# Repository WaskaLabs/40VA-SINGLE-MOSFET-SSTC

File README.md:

# 40VA-SINGLE-MOSFET-SSTC

If anyone would like to cooperate on the project or interrupt designs, have any questions or comments, feel free to contact me.

For more pictures and videos of the coil in action go to : https://www.instagram.com/waskalabs/

After posting some pictures of my completed design I have had quite a few people ask me for schematics / files / build info. The original intention of the design was to create a single pcb driver for any possible configuration of moderately low voltage transformer based tesla coils that I could use as a simple and quick platform for developing a variety of small desktop tesla coil designs and learn more about sstc operation. This design is a mixture of steve wards class e and mini sstc builds with some small modifications. For detials on the design go to (https://www.stevehv.4hv.org/sstc5.htm). I developed the V0 pcb design to be milled out at home using a pcb mill using a ~0.5mm endmill. You dont have to use a mill here - thats just what I designed the tolerances for. Any method of diy pcb production should work. After developing and testing the driver I put together a small test coil, tuned everything, and had a relatively impressive mini coil in about a day. The V0 design has a well annotated schematic and pcb with descriptions and information that will hopefully be easy for the novice to understand and recreate. There are many online resources for understanding the general operation of SSTCs so I will not be covering everything in detail here but only explaining the specs of my mini coil build here (links to more general resources below).

The V1 pcb design has been designed for proper pcb production and includes good high power design, external interrputer pins, better wire connection points, and has been made to be configurable for use with raw mains power using an external transformer as the low voltage source. As of writing this the pcbs are currently in production and have not arrived yet. When they do I will be testing mains versions of the design as well as some modular addons I have come up with and will post the designs here.

# mini coil design specifications  (V0 pcb):

Secondary coil = ~ 5.5 inch 34awg secondary coil wound on 3.5 inch pvc ~ 430khz (also tested with a ~6.5" 395khz coil which gave even better results)

Primary coil   = ~ 4.5 inch, 3 turns, 14 awg braided wire

Transformer    = UL1585 24v 40va (white and black wires for 120v)

555 interrupt  = ~ 7 - 480hz

Bus capacitors = 2 x 35v 22000uf caps

Mosfet         = IRFP460 (use for any high frequency coil)

After powering up the first coil and playing around with it a bit - it became immediately apparent that the 555 interrupter is not the way to go. I left it on the design as a simple way to get started - but I would not recommend it for continual use. The issue is the "On time" (time that the coil is powered up on each pulse) is much longer than necessary. The coil would ramp up and generate an arc, but would continue to burn away in continuous wave operation until being switched off by the low pulse of the 555. This can cause unnecessary strain on the mosfet, drains the bus caps, and also takes away from the aesthetic of the larger arcs. My solution to this was to remove the 555 chip and solder a 3 pin male to female dupont wire to the chip socket (interrupt, 12v, gnd pins) and run it into an arduino nano clone (pin 9, vin, gnd, respectively). The arduino should be programmed to give an on-time of between 1 - 5 milliseconds (I have stuck with 2 ms). I haave decided to add a potentiometer to vary the off time of the design to cycle between 2 - 1000 hz. The arduino tone library was also used successfully create audio output.

I will not be adding any more detail about the interrupter designs until the V1 pcbs are complete. Once they are in and test coils are built I will be making various interrupter addons such as staccato mode, isolated audio input, multiple potentiometers for varied on and off times over a given range, etc. And will post finished developments here.

If you decided to use an atx power supply as a case like I did. Be sure to keep the primary coil atleast 1-2 inches away from the metal surface of the case as the steel will interfere with the coil and significantly reduce performance. I 3D printed a coil standoff for this

For more detailed explainations of sstc operation & design:

https://www.stevehv.4hv.org/sstcindex.htm

https://www.loneoceans.com/labs/#

http://kaizerpowerelectronics.dk/

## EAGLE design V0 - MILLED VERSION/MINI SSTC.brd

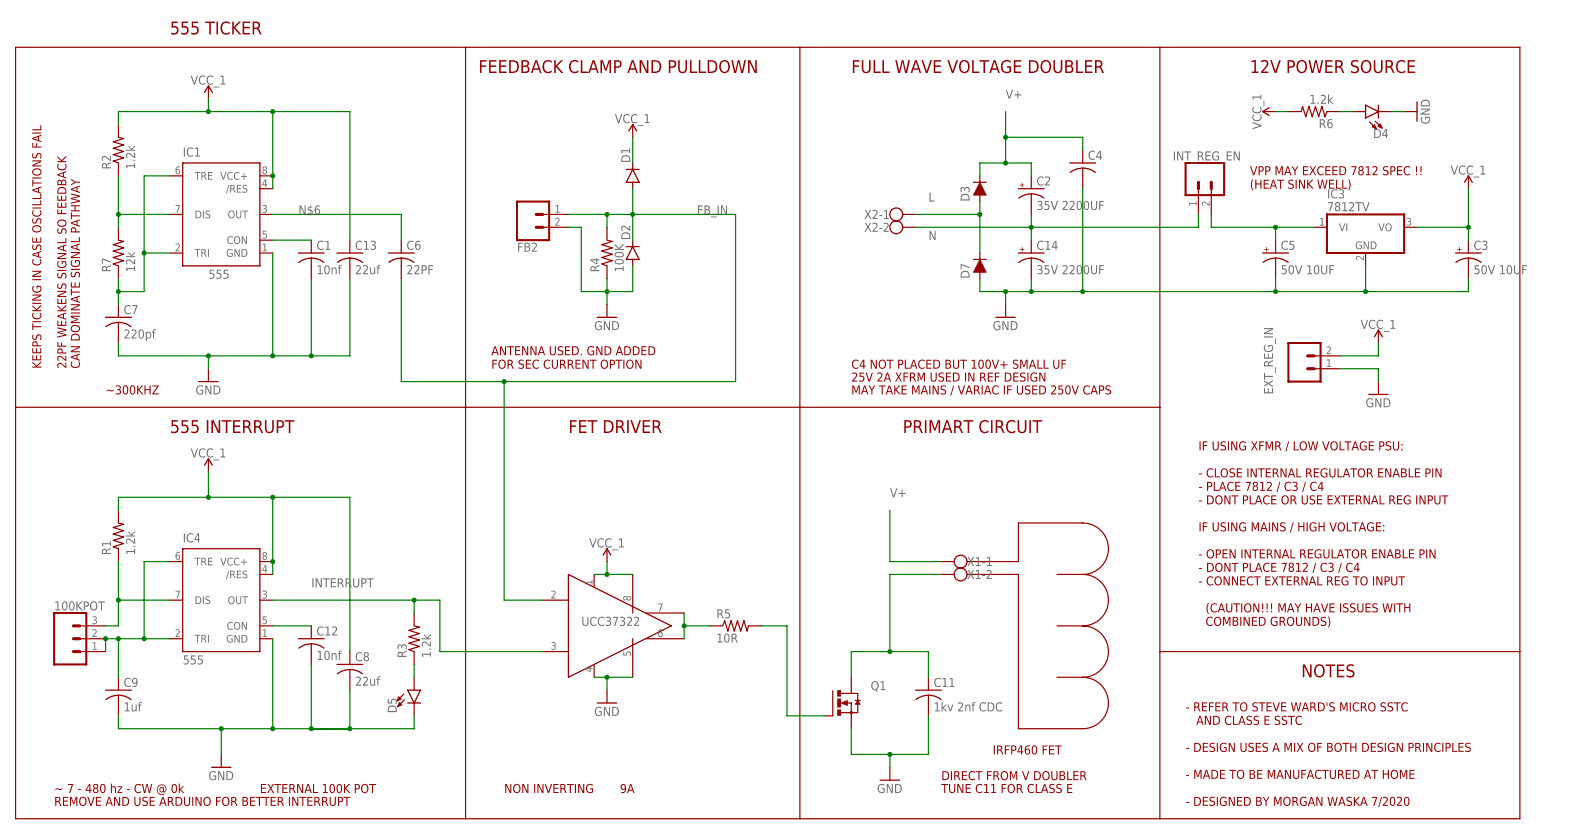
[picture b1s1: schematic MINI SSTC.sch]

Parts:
100KPOT: 455-1750-1-ND; 1X03
C1, C12: 10nf; C025-040X050
C2, C14: 35V 2200UF; E7,5-18
C3, C5: 50V 10UF; E2,5-5
C4: C-US025-040X050; C025-040X050
C6: 22PF; C025-040X050
C7: 220pf; C025-040X050
C8, C13: 22uf; C025-040X050
C9: 1uf; C025-040X050
C11: 1kv 2nf CDC; C150-054X183
D1, D2: 1N4148DO35-7; DO35-7
D3, D7: MUR460; DIODE-1N4001-KIT
D4, D5: LED5MM; LED_5MM
EXT_REG_IN: CONN_02; 1X02
FB2: CONN_02; 1X02
IC1, IC4: 555; DIP08-KIT
IC2: UCC37322; DIL08
IC3: 7812TV; TO220V
INT_REG_EN: CONN_02; 1X02
Q1: IRFP460; TO247BV
R1, R2, R3, R6: 1.2k; 0207/9
R4: 100K; 0207/9
R5: 10R; 0207/9
R7: 12k; 0207/9
X1, X2: W237-102

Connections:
555CONA: C1.1, IC1.5 (CON)
555CONB: C12.1, IC4.5 (CON)
FB_IN: C6.2, D1.A, D2.C, FB2.1, IC2.2 (2_IN), R4.2
GND: C1.2, C3.-, C4.2, C5.-, C7.2, C8.2, C9.2, C11.2, C12.2, C13.2, C14.-, D2.A, D4.K (C), D5.K (C), D7.A, EXT_REG_IN.1, FB2.2, IC1.1 (GND), IC2.4 (4_AGND), IC2.5 (5_PGND), IC3.2 (GND), IC4.1 (GND), Q1.S, R4.1
INTERRUPT: IC2.3 (3_ENBL), IC4.3 (OUT), R3.2
L: D3.A, D7.C, X2.1
N: C2.-, C14.+, INT_REG_EN.1, X2.2
unnamed: Q1.G, R5.2
unnamed: D5.A, R3.1
unnamed: C11.1, Q1.D, X1.2
unnamed: D4.A, R6.1
unnamed: C5.+, IC3.1 (VI), INT_REG_EN.2
unnamed: C6.1, IC1.3 (OUT)
unnamed: IC2.6 (6_OUT), IC2.7 (7_OUT), R5.1
RR555A: IC1.7 (DIS), R2.1, R7.2
RR555B: 100KPOT.3, IC4.7 (DIS), R1.1
TRIG555A: C7.1, IC1.2 (TRI), IC1.6 (TRE), R7.1
TRIG555B: 100KPOT.1, 100KPOT.2, C9.1, IC4.2 (TRI), IC4.6 (TRE)
V+: C2.+, C4.1, D3.C, X1.1
VCC_1: C3.+, C8.1, C13.1, D1.C, EXT_REG_IN.2, IC1.4 (/RES), IC1.8 (VCC+), IC2.1 (1_VDD), IC2.8 (8_VDD), IC3.3 (VO), IC4.4 (/RES), IC4.8 (VCC+), R1.2, R2.2, R6.2

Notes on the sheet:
UCC37322
555 TICKER
555 INTERRUPT
FEEDBACK CLAMP AND PULLDOWN
FET DRIVER
PRIMART CIRCUIT
FULL WAVE VOLTAGE DOUBLER
12V POWER SOURCE
NON INVERTING
~ 7 - 480 hz - CW @ 0k
EXTERNAL 100K POT
~300KHZ
KEEPS TICKING IN CASE OSCILLATIONS FAIL
ANTENNA USED. GND ADDED FOR SEC CURRENT OPTION
25V 2A XFRM USED IN REF DESIGN
MAY TAKE MAINS / VARIAC IF USED 250V CAPS
IF USING XFMR / LOW VOLTAGE PSU: - CLOSE INTERNAL REGULATOR ENABLE PIN - PLACE 7812 / C3 / C4 - DONT PLACE OR USE EXTERNAL REG INPUT IF USING MAINS / HIGH VOLTAGE: - OPEN INTERNAL REGULATOR ENABLE PIN - DONT PLACE 7812 / C3 / C4 - CONNECT EXTERNAL REG TO INPUT (CAUTION!!! MAY HAVE ISSUES WITH COMBI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
DIRECT FROM V DOUBLER
IRFP460 FET
NOTES
- REFER TO STEVE WARD'S MICRO SSTC AND CLASS E SSTC - DESIGN USES A MIX OF BOTH DESIGN PRINCIPLES - MADE TO BE MANUFACTURED AT HOME - DESIGNED BY MORGAN WASKA 7/2020
REMOVE AND USE ARDUINO FOR BETTER INTERRUPT
C4 NOT PLACED BUT 100V+ SMALL UF
VPP MAY EXCEED 7812 SPEC !! (HEAT SINK WELL)
TUNE C11 FOR CLASS E
22PF WEAKENS SIGNAL SO FEEDBACK CAN DOMINATE SIGNAL PATHWAY

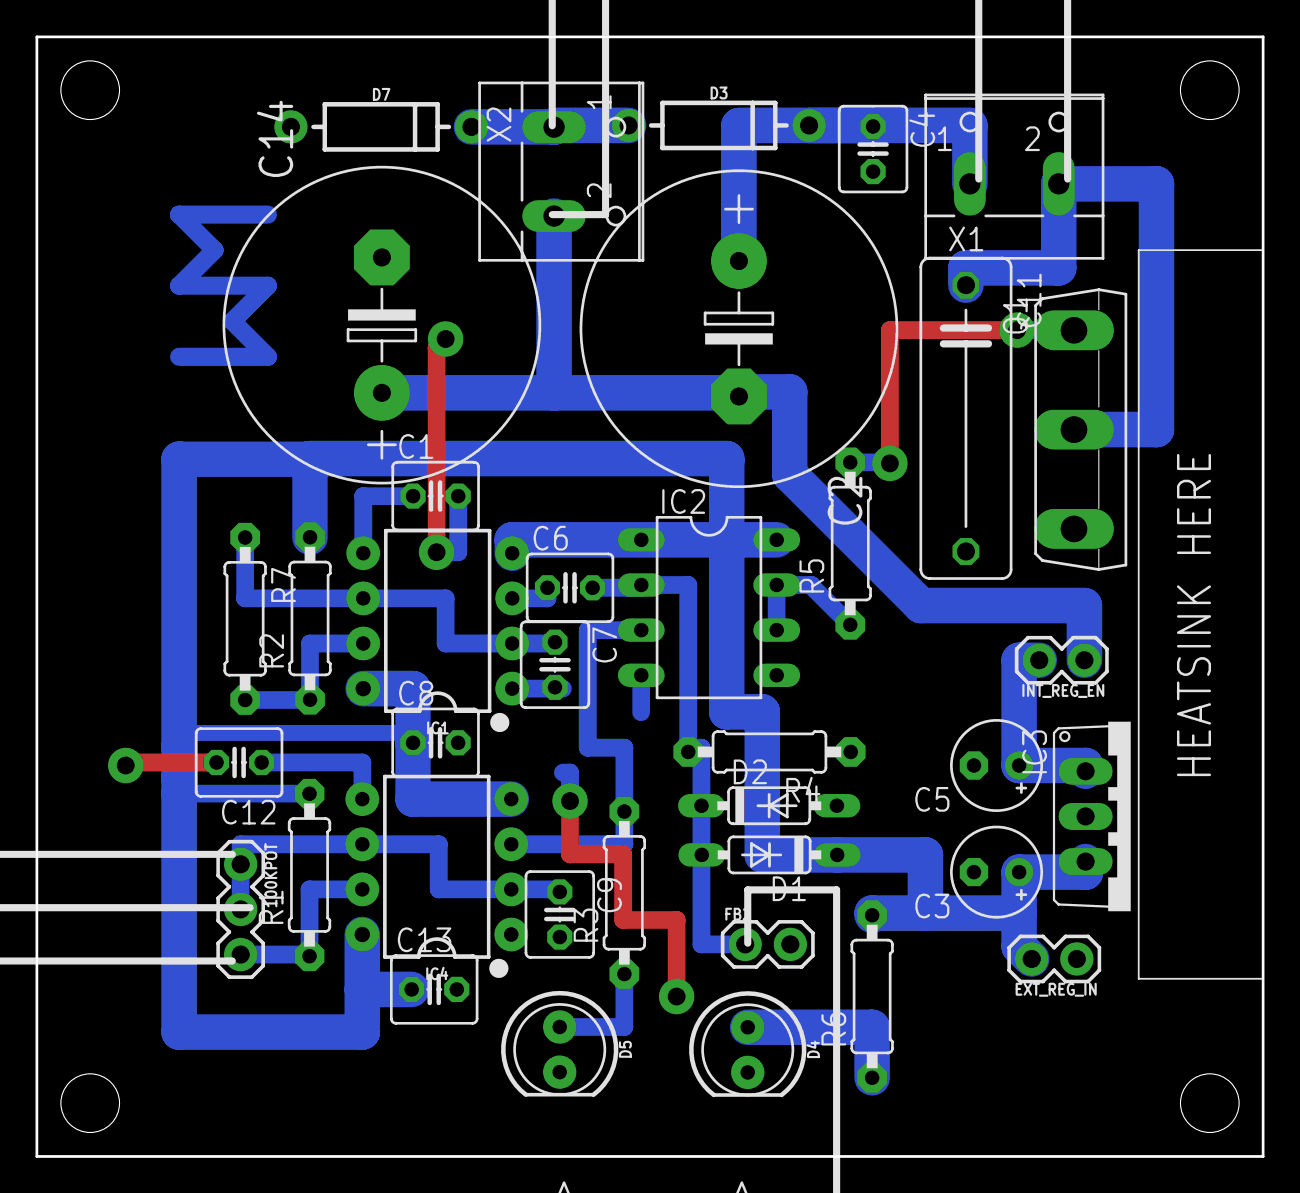
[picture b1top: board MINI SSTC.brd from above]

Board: 2 copper layers, 69.0 x 63.0 mm, 37 parts (0 on the bottom side), 20 nets.

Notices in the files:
parts and their libraries:
SparkFun-Connectors: Licensing: Creative Commons ShareAlike 4.0 International - https://creativecommons.org/licenses/by-sa/4.0
